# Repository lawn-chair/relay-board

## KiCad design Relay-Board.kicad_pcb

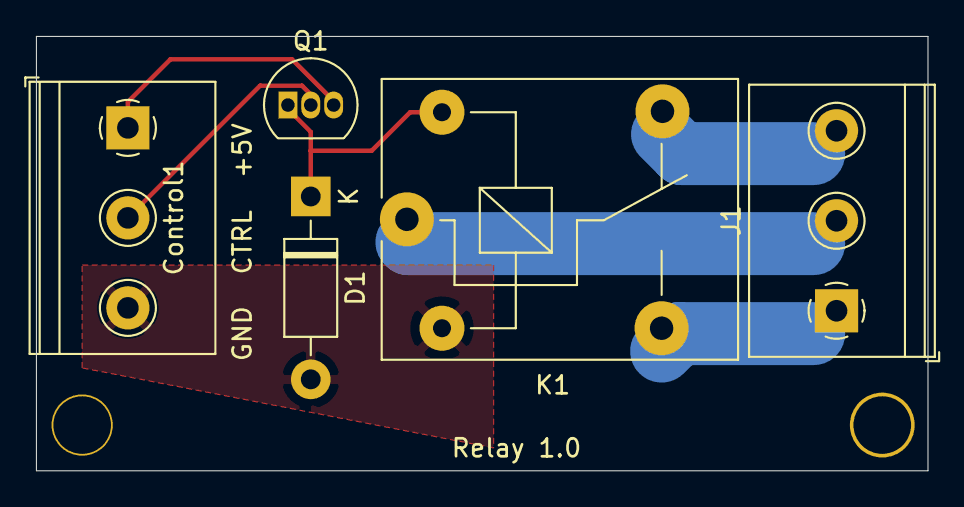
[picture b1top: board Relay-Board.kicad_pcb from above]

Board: 2 copper layers, 49.5 x 24.1 mm, 7 parts (0 on the bottom side), 7 nets.

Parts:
 : SolderWirePad_1x01_Drill0.8mm
 #2: SolderWirePad_1x01_Drill0.8mm
Control1: Screw_Terminal_01x03; TerminalBlock_Philmore_TB133_1x03_P5.00mm_Horizontal
D1: 1N4001; D_DO-41_SOD81_P10.16mm_Horizontal
J1: Screw_Terminal_01x03; TerminalBlock_Philmore_TB133_1x03_P5.00mm_Horizontal
K1: SANYOU_SRD_Form_C; Relay_SPDT_SANYOU_SRD_Series_Form_C
Q1: 2N3904; TO-92_Inline

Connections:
/5V: Control1.1, Q1.3
/COM: J1.2, K1.1
/GND: Control1.3, D1.2, K1.2
/IO: Control1.2, Q1.2
/NC: J1.3, K1.4
/NO: J1.1, K1.3
unnamed: D1.1, K1.5, Q1.1

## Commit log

2019-05-05 Updated pcb
2020-03-30 Added STL for enclosure
